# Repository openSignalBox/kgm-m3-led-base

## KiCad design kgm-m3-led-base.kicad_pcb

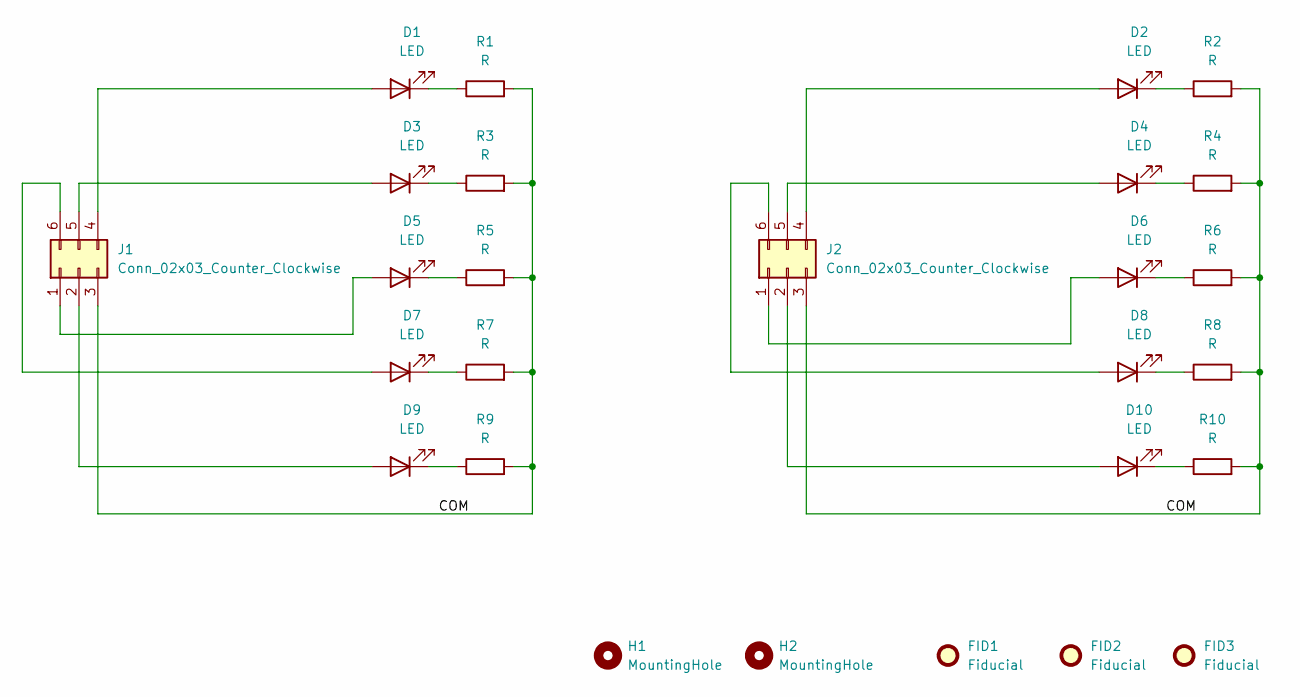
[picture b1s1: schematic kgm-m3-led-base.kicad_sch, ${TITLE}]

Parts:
D1, D2, D3, D4, D5, D6, D7, D8, D9, D10: LED; LED_D5.0mm
FID1, FID2, FID3: Fiducial; Fiducial_0.75mm_Mask1.5mm
H1, H2: MountingHole; MountingHole_3.2mm_M3
J1, J2: Conn_02x03_Counter_Clockwise; PinHeader_2x03_P2.54mm_Vertical_SMD
R1, R2, R3, R4, R5, R6, R7, R8, R9, R10: R; R_0805_2012Metric_Pad1.20x1.40mm_HandSolder

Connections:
/COM: J1.3, J2.3, R1.2, R2.2, R3.2, R4.2, R5.2, R6.2, R7.2, R8.2, R9.2, R10.2
unnamed: D1.2 (A), J1.4
unnamed: D1.1 (K), R1.1
unnamed: D2.2 (A), J2.4
unnamed: D2.1 (K), R2.1
unnamed: D3.2 (A), J1.5
unnamed: D3.1 (K), R3.1
unnamed: D4.2 (A), J2.5
unnamed: D4.1 (K), R4.1
unnamed: D5.2 (A), J1.1
unnamed: D5.1 (K), R5.1
unnamed: D6.2 (A), J2.1
unnamed: D6.1 (K), R6.1
unnamed: D7.2 (A), J1.6
unnamed: D7.1 (K), R7.1
unnamed: D8.2 (A), J2.6
unnamed: D8.1 (K), R8.1
unnamed: D9.2 (A), J1.2
unnamed: D9.1 (K), R9.1
unnamed: D10.2 (A), J2.2
unnamed: D10.1 (K), R10.1

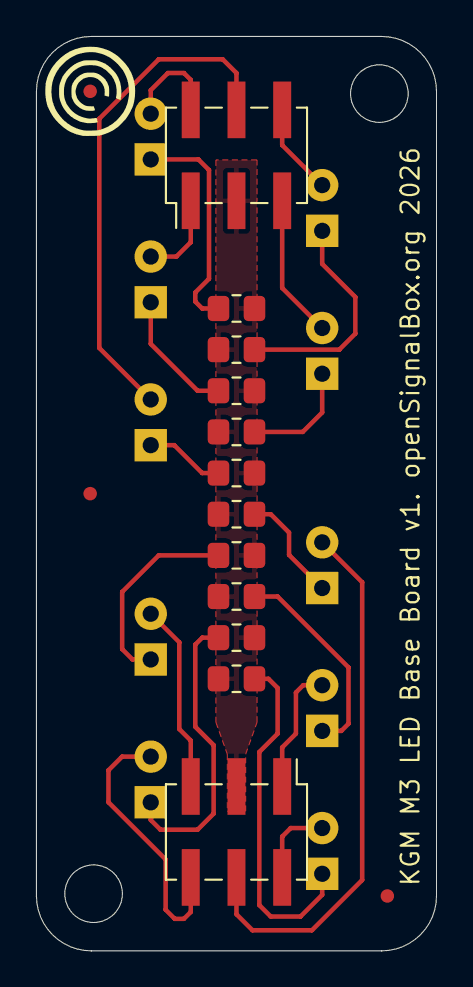
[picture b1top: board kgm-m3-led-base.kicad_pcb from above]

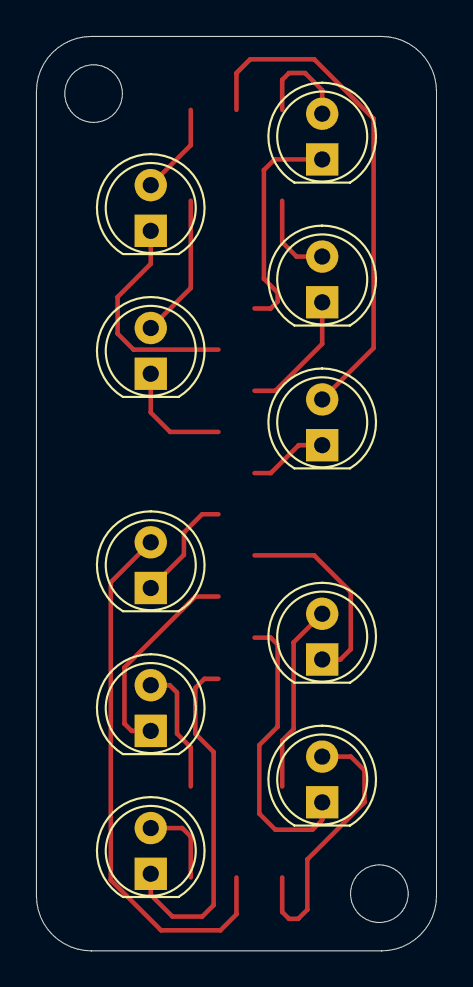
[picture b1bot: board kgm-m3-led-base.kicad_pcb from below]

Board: 2 copper layers, 22.2 x 50.8 mm, 27 parts (10 on the bottom side), 21 nets.

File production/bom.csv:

Designator,Footprint,Quantity,Value,LCSC Part #
"D1, D10, D2, D3, D4, D5, D6, D7, D8, D9",LED_D5.0mm,10,LED,
"J1, J2",PinHeader_2x03_P2.54mm_Vertical_SMD,2,Conn_02x03_Counter_Clockwise,
"R1, R10, R2, R3, R4, R5, R6, R7, R8, R9",0805,10,R,

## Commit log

2026-05-19 v1 commit
2026-05-19 Added fiducials to PCB and updated silk to add .org
2026-05-19 Updated production files
2026-05-20 Redesigned connector, added spacer model
